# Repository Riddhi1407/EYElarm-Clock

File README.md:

# EYElarm Clock
***
An alarm clock that uses image detection to put off alarm. It asks the person using it to show a specific household object to put off alarm, helping them wake up by forcing them to do an activity.

**Schematic**

**PCB**

**CAD**

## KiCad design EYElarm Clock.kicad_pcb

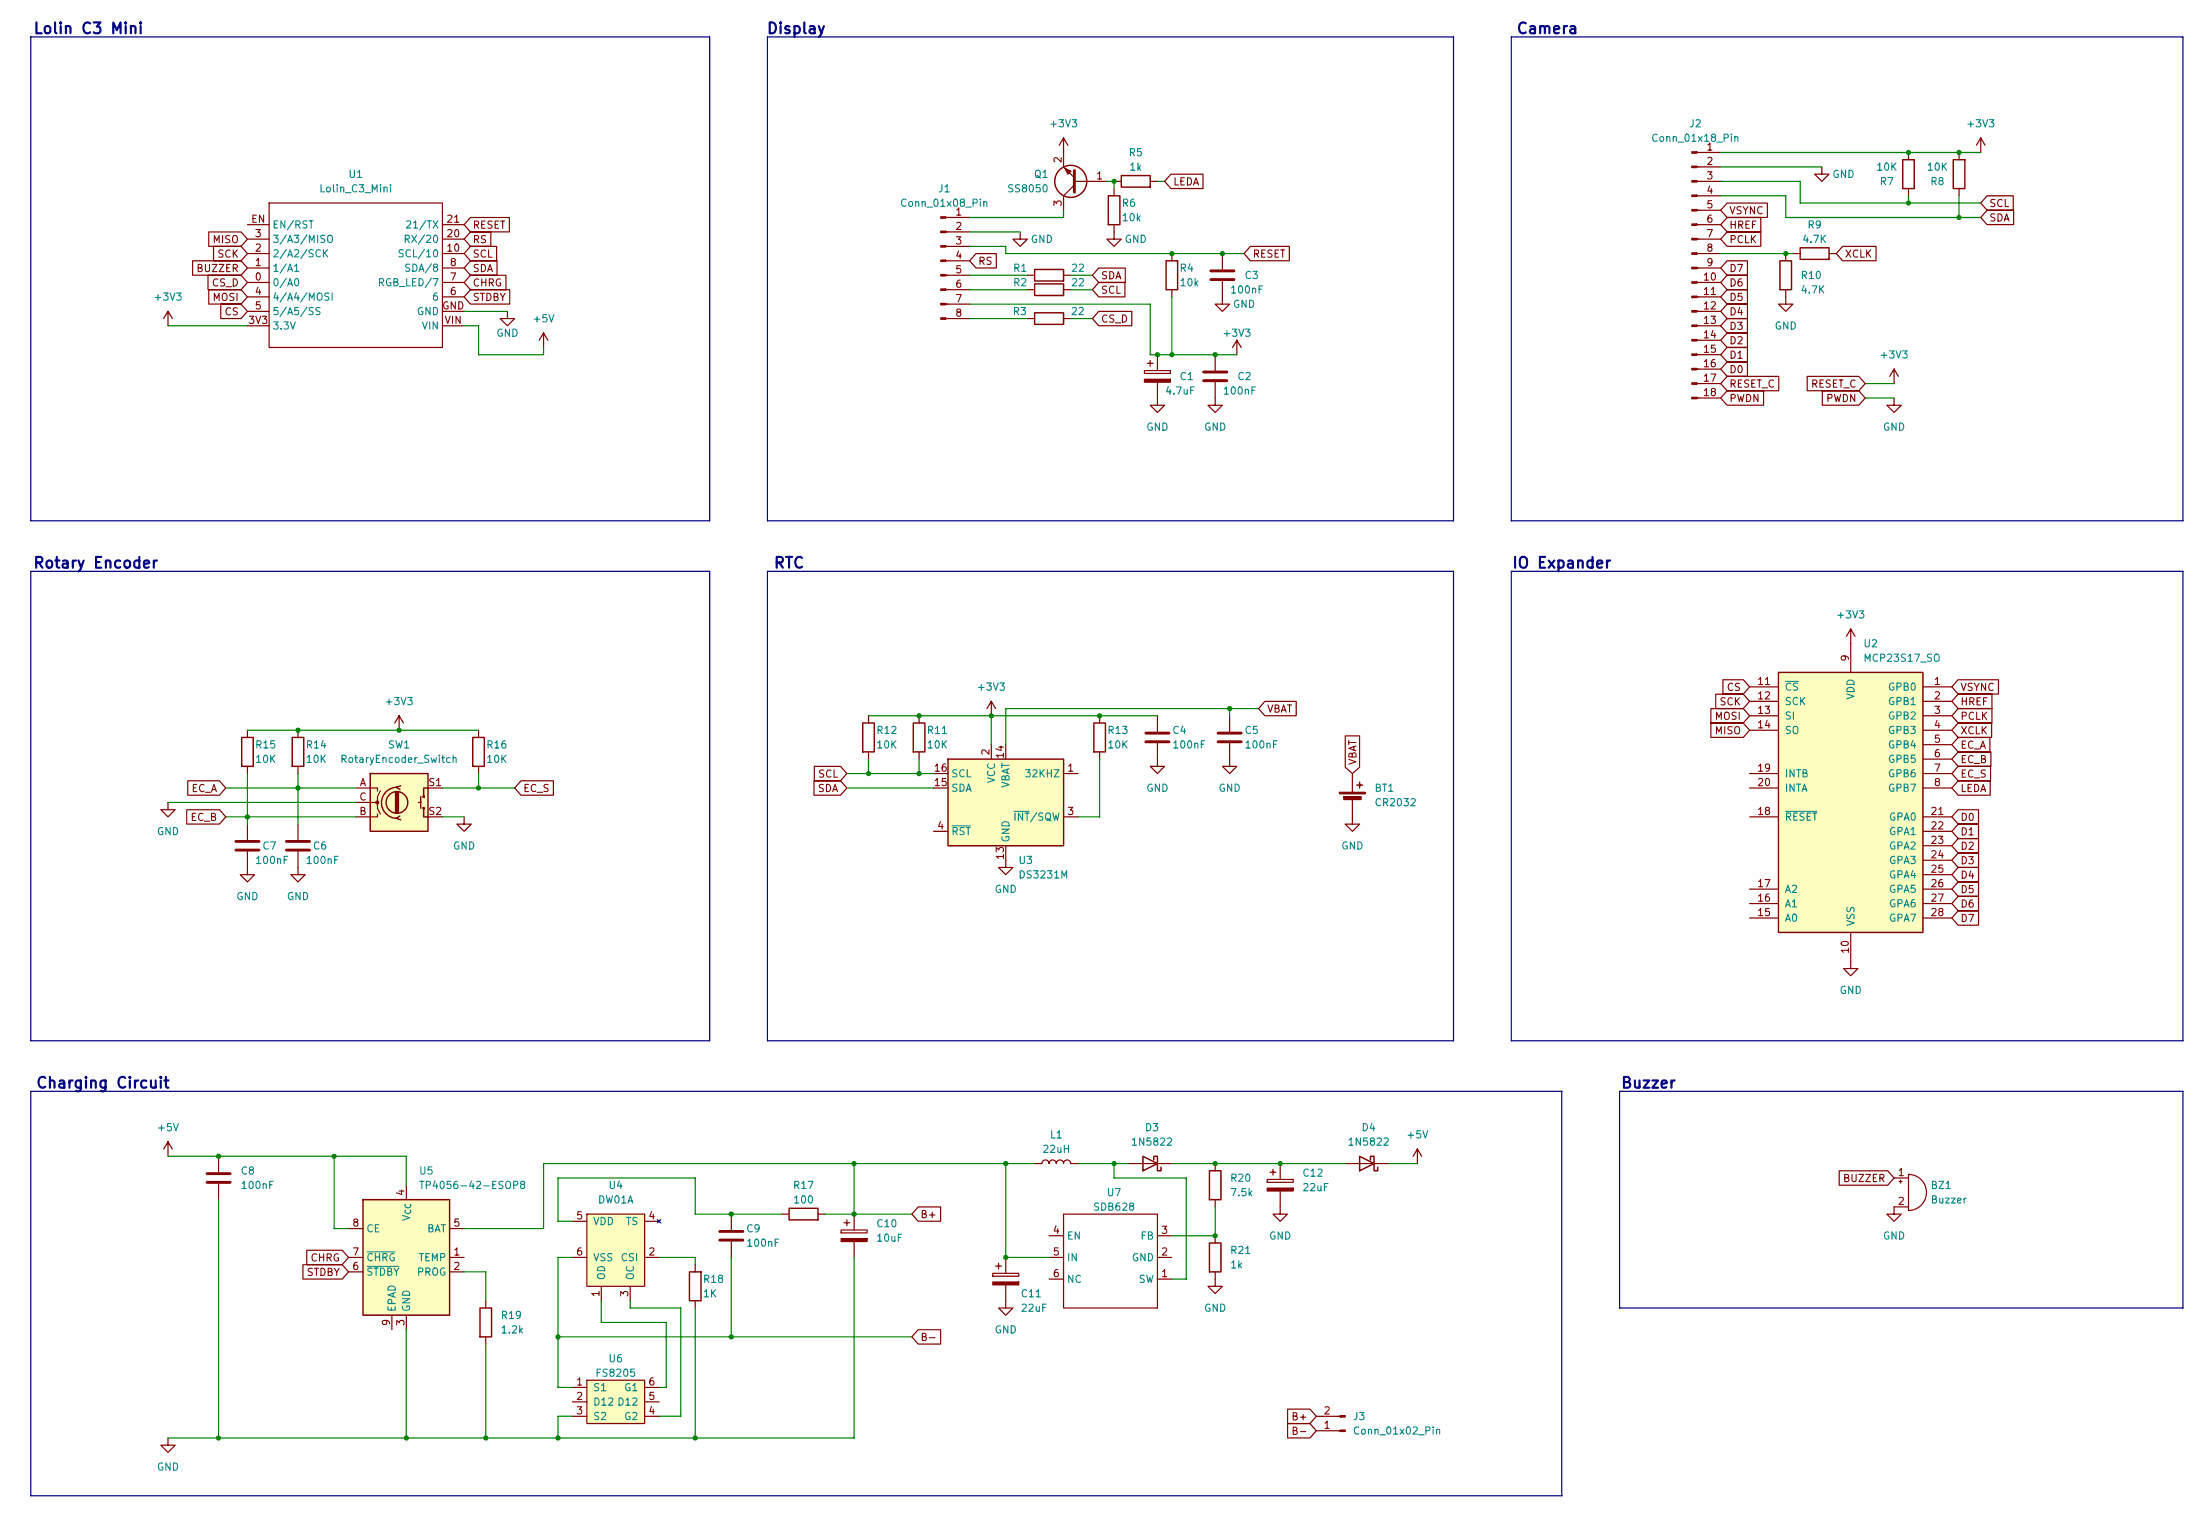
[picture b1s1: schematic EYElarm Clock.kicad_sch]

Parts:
BT1: CR2032; BatteryHolder_MYOUNG_BS-07-A1BJ001_CR2032
BZ1: Buzzer; Buzzer_12x9.5RM7.6
C1: 4.7uF; CP_Radial_D10.0mm_P5.00mm
C2, C3, C4, C5, C6, C7, C8, C9: 100nF; C_Disc_D6.0mm_W2.5mm_P5.00mm
C10: 10uF; CP_Radial_D10.0mm_P5.00mm
C11, C12: 22uF; CP_Radial_D10.0mm_P5.00mm
D3, D4: 1N5822; D_DO-201AD_P15.24mm_Horizontal
J1: Conn_01x08_Pin; TE_0-1734839-8_1x08-1MP_P0.5mm_Horizontal
J2: Conn_01x18_Pin; TE_1-1734839-8_1x18-1MP_P0.5mm_Horizontal
J3: Conn_01x02_Pin; JST_EH_S2B-EH_1x02_P2.50mm_Horizontal
L1: 22uH; L_Radial_D8.7mm_P5.00mm_Fastron_07HCP
Q1: SS8050; SOT-23
R1, R2, R3: 22; R_Axial_DIN0207_L6.3mm_D2.5mm_P7.62mm_Horizontal
R4, R6: 10k; R_Axial_DIN0207_L6.3mm_D2.5mm_P7.62mm_Horizontal
R5, R21: 1k; R_Axial_DIN0207_L6.3mm_D2.5mm_P7.62mm_Horizontal
R7, R8, R11, R12, R13, R14, R15, R16: 10K; R_Axial_DIN0207_L6.3mm_D2.5mm_P7.62mm_Horizontal
R9, R10: 4.7K; R_Axial_DIN0207_L6.3mm_D2.5mm_P7.62mm_Horizontal
R17: 100; R_Axial_DIN0207_L6.3mm_D2.5mm_P7.62mm_Horizontal
R18: 1K; R_Axial_DIN0207_L6.3mm_D2.5mm_P7.62mm_Horizontal
R19: 1.2k; R_Axial_DIN0207_L6.3mm_D2.5mm_P7.62mm_Horizontal
R20: 7.5k; R_Axial_DIN0207_L6.3mm_D2.5mm_P7.62mm_Horizontal
SW1: RotaryEncoder_Switch; ROT_Alps_EC11E-Switch
U1: Lolin_C3_Mini; Lolin C3 Mini
U2: MCP23S17_SO; SOIC-28W_7.5x17.9mm_P1.27mm
U3: DS3231M; SOIC-16W_7.5x10.3mm_P1.27mm
U4: DW01A; SOT-23-6; LCSC C61503
U5: TP4056-42-ESOP8; SOIC-8-1EP_3.9x4.9mm_P1.27mm_EP2.41x3.3mm_ThermalVias
U6: FS8205; SOT-23-6; LCSC C32254
U7: SDB628; SOT-23-6

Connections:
+5V: C8.1, D4.1 (K), U1.VIN, U5.4 (V_{CC}), U5.8 (CE)
B+: C10.1, C11.1, J3.2, L1.1, R17.2, U5.5 (BAT), U7.5 (IN)
B-: C9.2, J3.1, U4.6 (VSS), U6.1 (S1)
BUZZER: BZ1.1 (+), U1.1 (1/A1)
CHRG: U1.7 (RGB_LED/7), U5.7 (~CHRG)
CS: U1.5 (5/A5/SS), U2.11 (~CS)
CS_D: R3.2, U1.0 (0/A0)
D0: J2.16, U2.21 (GPA0)
D1: J2.15, U2.22 (GPA1)
D2: J2.14, U2.23 (GPA2)
D3: J2.13, U2.24 (GPA3)
D4: J2.12, U2.25 (GPA4)
D5: J2.11, U2.26 (GPA5)
D6: J2.10, U2.27 (GPA6)
D7: J2.9, U2.28 (GPA7)
EC_A: C6.1, R14.2, SW1.A, U2.5 (GPB4)
EC_B: C7.1, R15.2, SW1.B, U2.6 (GPB5)
EC_S: R16.2, SW1.S1, U2.7 (GPB6)
HREF: J2.6, U2.2 (GPB1)
LEDA: R5.2, U2.8 (GPB7)
MISO: U1.3 (3/A3/MISO), U2.14 (SO)
MOSI: U1.4 (4/A4/MOSI), U2.13 (SI)
unnamed: D3.2 (A), L1.2, U7.1 (SW)
unnamed: C12.1, D3.1 (K), D4.2 (A), R20.1
unnamed: J1.1, Q1.3 (C)
unnamed: J1.5, R1.1
unnamed: J1.6, R2.1
unnamed: J1.8, R3.1
unnamed: J2.8, R9.1, R10.1
unnamed: Q1.1 (B), R5.1, R6.1
unnamed: R13.2, U3.3 (~INT/SQW)
unnamed: R18.2, U4.2 (CSI)
unnamed: U4.3 (OC), U6.4 (G2)
unnamed: U4.1 (OD), U6.6 (G1)
unnamed: C9.1, R17.1, U4.5 (VDD)
unnamed: R19.1, U5.2 (PROG)
unnamed: R20.2, R21.1, U7.3 (FB)
PCLK: J2.7, U2.3 (GPB2)
PWDN: BT1.2 (-), BZ1.2 (-), C1.2, C2.2, C3.2, C4.2, C5.2, C6.2, C7.2, C8.2, C10.2, C11.2, C12.2, J1.2, J2.2, J2.18, R6.2, R10.2, R18.1, R19.2, R21.2, SW1.C, SW1.S2, U1.GND, U2.10 (VSS), U3.5 (GND), U3.6 (GND), U3.7 (GND), U3.8 (GND), U3.9 (GND), U3.10 (GND), U3.11 (GND), U3.12 (GND), U3.13 (GND), U5.3 (GND), U6.3 (S2)
RESET: C3.1, J1.3, R4.2, U1.21 (21/TX)
RESET_C: C1.1, C2.1, C4.1, J1.7, J2.1, J2.17, Q1.2 (E), R4.1, R7.2, R8.2, R11.1, R12.1, R13.1, R14.1, R15.1, R16.1, U1.3V3 (3.3V), U2.9 (VDD), U3.2 (VCC)
RS: J1.4, U1.20 (RX/20)
SCK: U1.2 (2/A2/SCK), U2.12 (SCK)
SCL: J2.3, R2.2, R7.1, R11.2, R12.2, U1.10 (SCL/10), U3.16 (SCL)
SDA: J2.4, R1.2, R8.1, U1.8 (SDA/8), U3.15 (SDA)
STDBY: U1.6, U5.6 (~STDBY)
VBAT: BT1.1 (+), C5.1, U3.14 (VBAT)
VSYNC: J2.5, U2.1 (GPB0)
XCLK: R9.2, U2.4 (GPB3)

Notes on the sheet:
Rotary Encoder
RTC
Buzzer
IO Expander
Display
Charging Circuit
Camera
Lolin C3 Mini

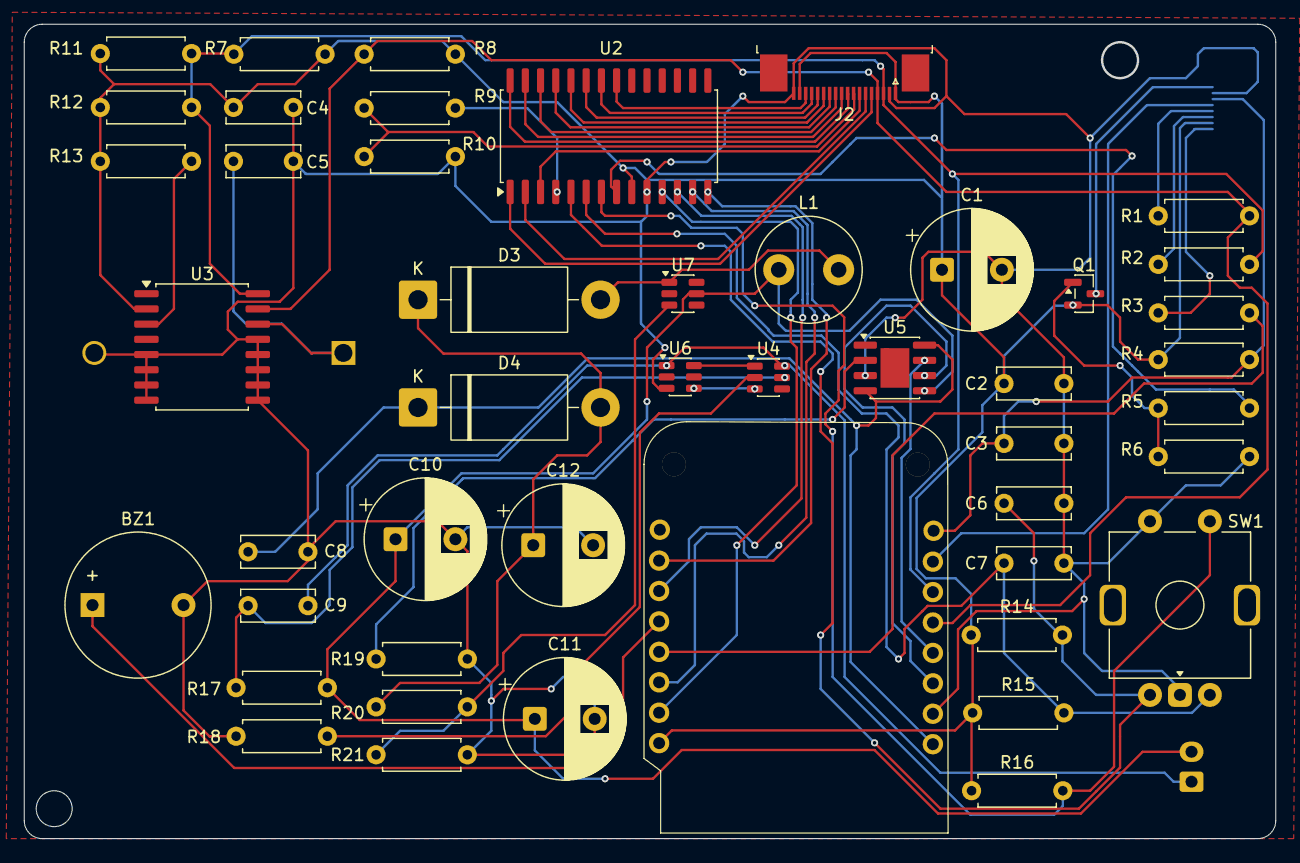
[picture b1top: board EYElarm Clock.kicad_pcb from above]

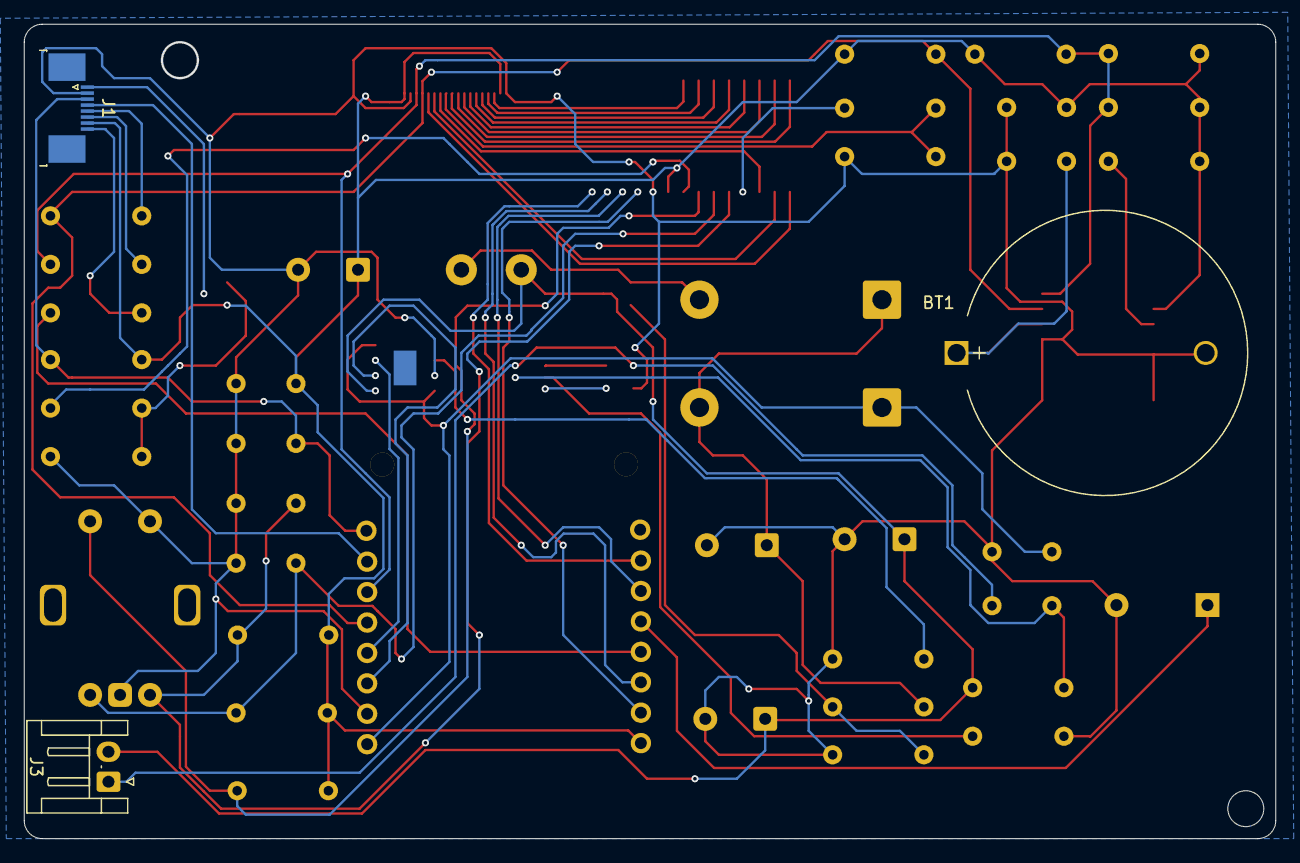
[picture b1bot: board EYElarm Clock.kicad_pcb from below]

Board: 2 copper layers, 104.5 x 68.0 mm, 50 parts (3 on the bottom side), 49 nets.
